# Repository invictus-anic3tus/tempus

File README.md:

<div align="center" width=100%>

  <p display="inline">

  <a href="https://hackclub.com/"></img></a>

  </p>

  <h1></h1>

  <p>
    An open source, ESP32-based smartwatch!
  </p>
</div>

<sub>This work is licensed under a
[Creative Commons Attribution-NonCommercial 4.0 International License](https://creativecommons.org/licenses/by-nc/4.0/).
</sub>

## Table of Contents

- [About](#about)
- [Features](#features)
- [Specifications](#specifications)
- [Bill of Materials](#bill-of-materials)
- [Contributing](#contributing)

## About

My name is Anicetus, and I love hardware. The Anicept Tempus is my newest addition to my brand, and the first devboard PCB! There are others out there, and many are probably much better. But I felt it was high time I had one of my _own._ It might not beat the competition in price, features, quality, you name it; but there comes a certain satisfaction when you can wear (more like tout at this point) a semi-stylish, functional, and helpful item that you can point to and confidently say: "I created this from scratch."

And so, the Tempus is a small yet powerful ESP32 devboard PCB + case, equipped with all the features that a modern digital smartwatch would need. Fully able to track steps and gestures, voice text, make beeps and alerts with a buzzer, power a round touchscreen, and, of course, tell time, it's the ideal replacement for a multi-hundred-dollar smartwatch with the same features.

## Features

Speaking of features, this watch is equipped with the following:
- A precise, quick gyroscope/accelerometer for hand tracking
- WiFi and Bluetooth for connecting to your phone to receive texts and calls, as well as control music apps such as Spotify
- An RTC (Real Time Clock) chip capable of maintaining incredibly accurate time
- A vibration motor for alerts and ringtones
- A microphone for voice messaging or reminders. (Note: the watch doesn't have a speaker, so playing music, receiving calls, etc. must be done through headphones connected to a phone connected to the watch. Also, unfortunately the ESP32-S3 cannot be used as a microphone during calls, so for that you'll need to use your phone's built-in mic.)
- Two reprogrammable buttons, perfect for quick text replies, controlling music, or navigating to apps.
- A modern USB-C 2.0 charging and programming recepticle
- A 500mAh battery, to ensure minimal charging time
- A battery percentage monitor to ensure the watch never dies
- A 1.28" capacitive touch display

## How do I build this?

Good question! If you'd like to make the Tempus for yourself, there's a few things you should keep in mind:
1. You must have access to a 3D printer or be willing to pay for a printing service. TPU or another flexible filament is required for the watch band.
2. You must have access to soldering equipment and be skilled in soldering. This includes a hot air gun and solder paste.
3. This design necessitates a custom PCB. These can get expensive if you need to account for shipping or tariff costs.
4. This is _not_ a professional design! I'm a random guy from the internet who made a smartwatch design; if you want to make it for yourself, go ahead! But I am not responsible for any misuse or unintended happenings due to faulty design.
5. Commercial use is not allowed. You cannot make this watch to sell to anybody.

Alright! Now we can get into how to actually build it. First, download the gerber.zip file in the PCB_Production folder, go to your favorite PCB manufacturing service (JLCPCB and PCBWay are good) and upload it in their quote system. It should say four-layer PCB. Here are the settings to select:
(Make sure you know what you're doing before changing these! The color is self-explanatory, but colors other than green can be more expensive.)

Then, order the DigiKey parts in [this cart](https://www.digikey.com/short/2mbbn5n0) and the screen from [BuyDisplay](https://www.buydisplay.com/1-28-inch-tft-lcd-display-240x240-round-circle-screen-for-smart-watch) or [eBay](https://www.ebay.com/itm/305668452899?var=604666595108).

Next, 3D print the files in the CAD folder. Detailed assembly instructions coming soon; for now, please reference the full CAD design!

## Specifications

Nerd info incoming
- Main processor: ESP32-S3-Wroom-1
- Gyroscope/accelerometer: LSM6DSMTR
- RTC: DS3231M+
- Battery Charging: TPB4056B (A drop-in TP4056 replacement, available on DigiKey)
- Microphone: SPH0645LM4H-B
- Display: [1.28 inch 240x240 IPS TFT LCD Round Circle Capacitive Touch Screen](https://www.buydisplay.com/1-28-inch-tft-lcd-display-240x240-round-circle-screen-for-smart-watch)
- Main 3v3 Buck-Boost Converter: TPS63031DSKR

## Bill of Materials

|       Item       |  Price  |                                                  Link                                              | Shipping |
|------------------|---------|----------------------------------------------------------------------------------------------------|----------|
| PCB              | $2      | <https://jlcpcb.com>                                                                               | $3.18    |
| DigiKey Parts*   | $67.34  | <https://www.digikey.com/short/2mbbn5n0>                                                           | $6.99    |
| Screen           | $8.85   | <https://www.buydisplay.com/1-28-inch-tft-lcd-display-240x240-round-circle-screen-for-smart-watch> | $8.12    |
| Total            | $78.19  |                                                                                                    | $18.29   |

*Including subjective tariffs, taxes, etc. Also includes battery and solder paste.

An online DigiKey cart is available at <https://www.digikey.com/short/2mbbn5n0>.

### Grand Total: ±$96.48

(Recommended planned price: $100)

## Contributing

<sub>aha somebody wishes to help me i see</sub>

If you'd like to request changes, suggest additions, or forcefully make me edit things, feel free to contact me via email (`me at anicetus dot dev`, preferred) or Discord (anic3tus).

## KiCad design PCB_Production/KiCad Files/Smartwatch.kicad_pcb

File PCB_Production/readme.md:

PCB Source files (schematic, board layout, etc.)

As this watch was designed to be hand-soldered, the assembly files have not been tested. The BOM, however, does contain LCSC part numbers for every component on the PCB. The gerbers are tested and work correctly.

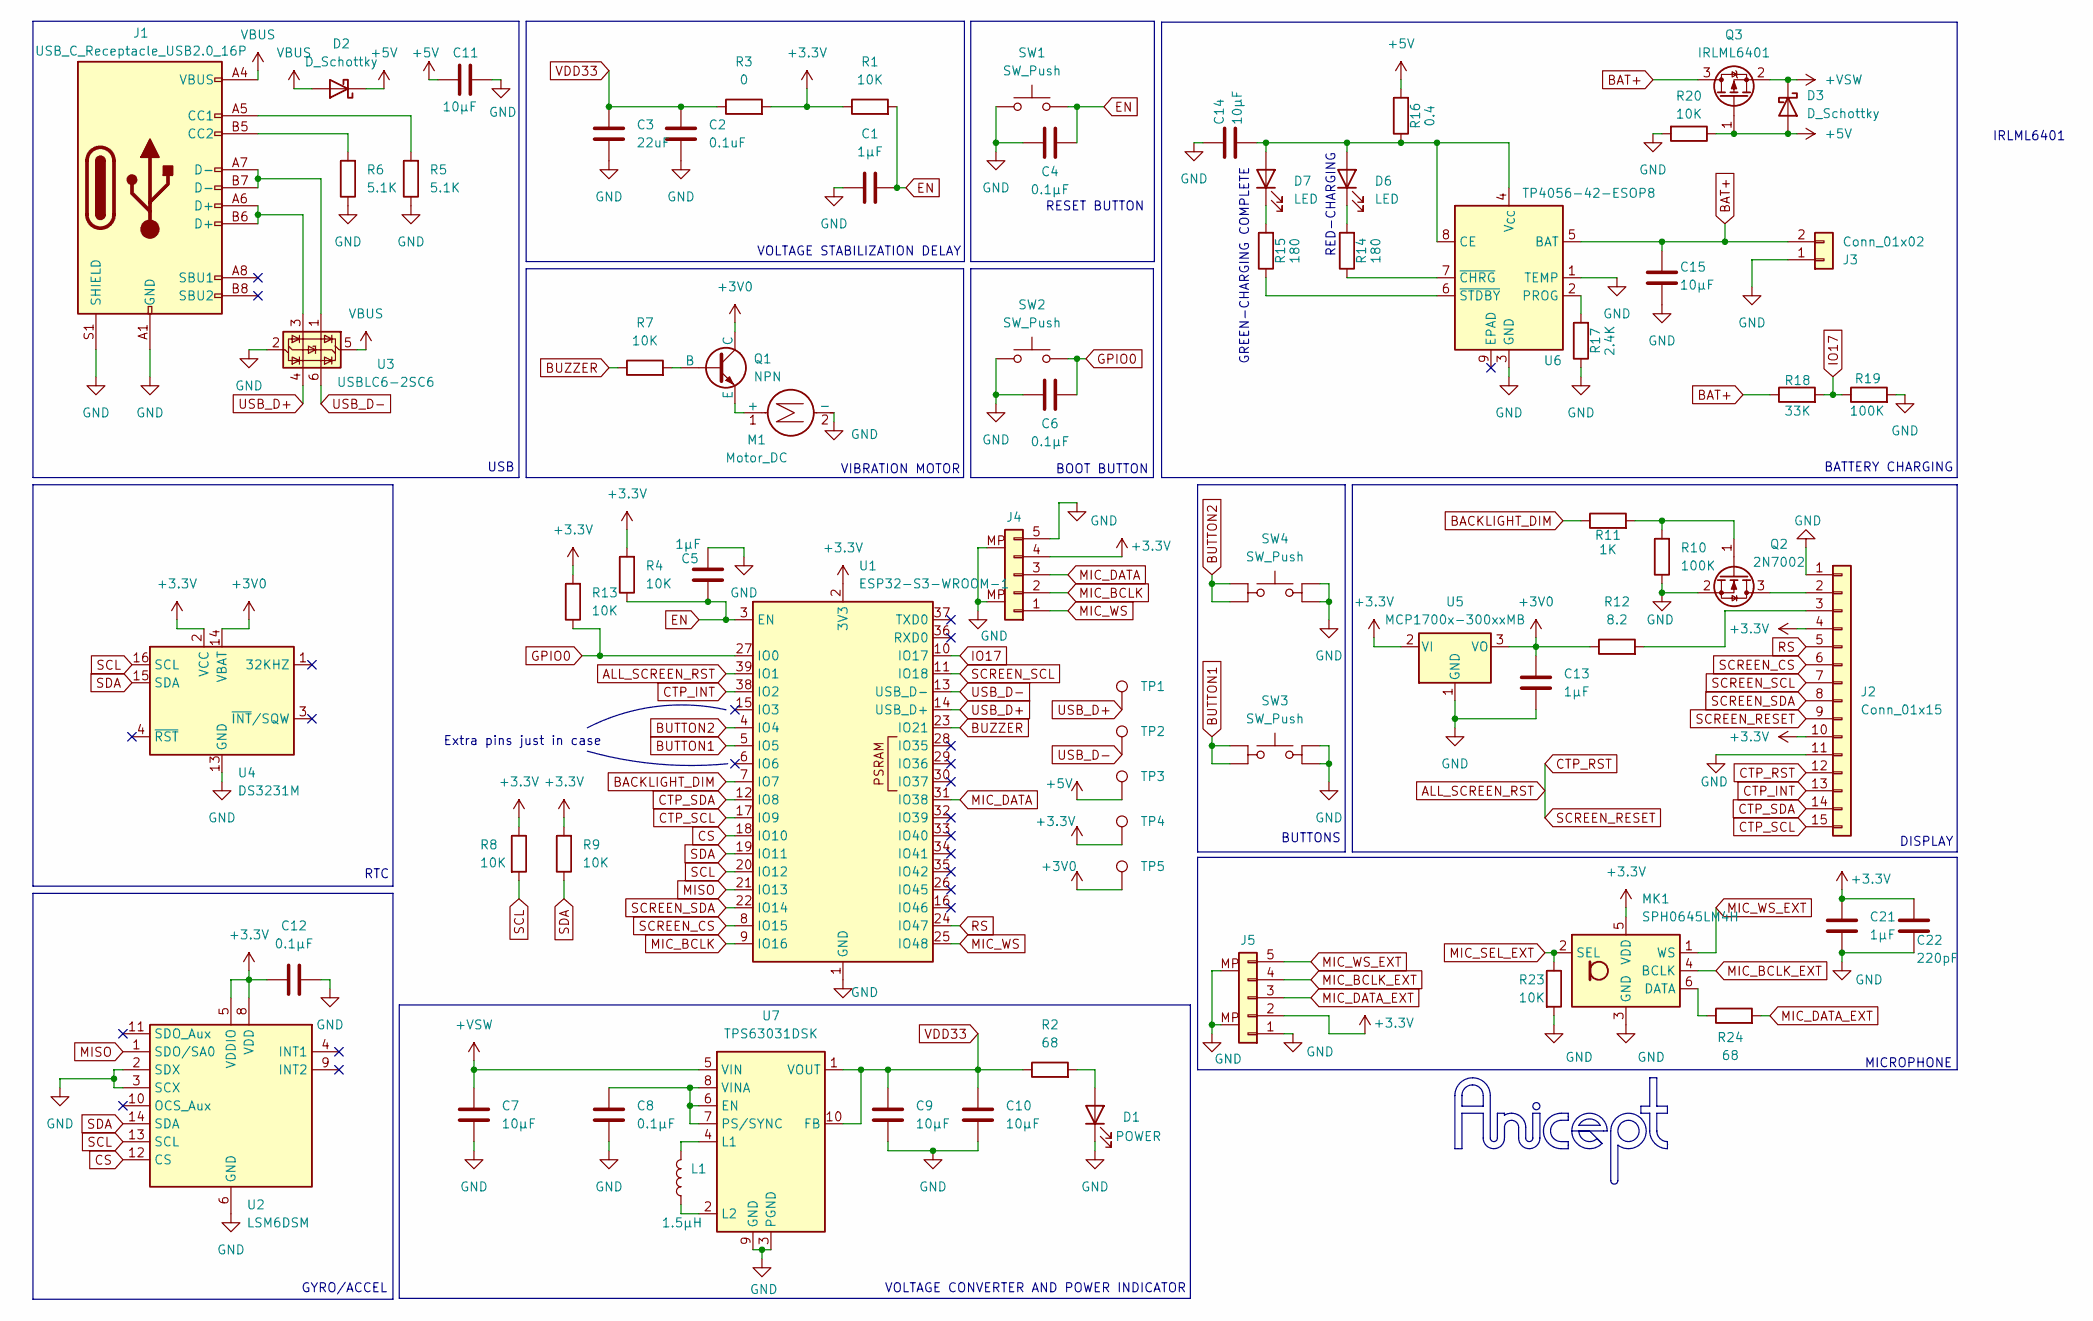
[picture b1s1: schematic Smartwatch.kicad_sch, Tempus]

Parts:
C1, C5, C13, C21: 1µF; C_0805_2012Metric
C2: 0.1uF; C_0805_2012Metric
C3: 22uF; C_0805_2012Metric
C4, C6, C8, C12: 0.1µF; C_0805_2012Metric
C7, C9, C10, C11, C14, C15: 10µF; C_0805_2012Metric
C22: 220pF; C_0805_2012Metric
D1: POWER; LED_0805_2012Metric
D2, D3: D_Schottky; D_SOD-123
D6, D7: LED; LED_0805_2012Metric
J1: USB_C_Receptacle_USB2.0_16P; USB_C_Receptacle_G-Switch_GT-USB-7010ASV
J2: Conn_01x15; Amphenol_F32Q-1A7x1-11015_1x15-1MP_P0.5mm_Horizontal
J3: Conn_01x02; JST_ZH_B2B-ZR_1x02_P1.50mm_Vertical
J4, J5: JST_SH_BM05B-SRSS-TB_1x05-1MP_P1.00mm_Vertical
L1: 1.5µH; IND_LQH3NPN1R5MJRL
M1: Motor_DC; TestPoint_Pad_1.5x1.5mm
MK1: SPH0645LM4H; Knowles_SPH0645LM4H-6_3.5x2.65mm
Q1: NPN; SOT-23
Q2: 2N7002; SOT-23
Q3: IRLML6401; SOT-23
R1, R4, R7, R8, R9, R13, R20, R23: 10K; R_0805_2012Metric
R2, R24: 68; R_0805_2012Metric
R3: 0; R_0805_2012Metric
R5, R6: 5.1K; R_0805_2012Metric
R10, R19: 100K; R_0805_2012Metric
R11: 1K; R_0805_2012Metric
R12: 8.2; R_0805_2012Metric
R14, R15: 180; R_0805_2012Metric
R16: 0.4; R_0805_2012Metric
R17: 2.4K; R_0805_2012Metric
R18: 33K; R_0805_2012Metric
SW1, SW2: SW_Push; SW-SMD_L3.9-W3.0-P4.45
SW3, SW4: SW_Push; SW_EVQ-P7C01P
TP1, TP2, TP3, TP4, TP5: TestPoint_Pad_1.0x1.0mm
U1: ESP32-S3-WROOM-1
U2: LSM6DSM; LGA-14_3x2.5mm_P0.5mm_LayoutBorder3x4y
U3: USBLC6-2SC6; SOT-23-6_Handsoldering
U4: DS3231M; SOIC-16W_7.5x10.3mm_P1.27mm
U5: MCP1700x-300xxMB; SOT-89-3
U6: TP4056-42-ESOP8; SOIC-8-1EP_3.9x4.9mm_P1.27mm_EP2.41x3.3mm_ThermalVias
U7: TPS63031DSK; WSON-10-1EP_2.5x2.5mm_P0.5mm_EP1.2x2mm_ThermalVias

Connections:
+3.3V: C12.2, C21.2, C22.2, J2.4, J2.10, J4.4, J5.2, MK1.5 (VDD), R1.1, R3.2, R4.2, R8.1, R9.2, R13.2, TP4.1, U1.2 (3V3), U2.5 (VDDIO), U2.8 (VDD), U4.2 (VCC), U5.2 (VI)
+3V0: C13.2, Q1.1 (C), R12.1, TP5.1, U4.14 (VBAT), U5.3 (VO)
+5V: C11.2, D2.1 (K), D3.2 (A), Q3.1 (G), R16.2, R20.1, TP3.1
+VSW: C7.2, D3.1 (K), Q3.2 (S), U7.5 (VIN)
ALL_SCREEN_RST: J2.9, J2.12, U1.39 (IO1)
BACKLIGHT_DIM: R11.1, U1.7 (IO7)
BAT+: C15.2, J3.2, Q3.3 (D), R18.1, U6.5 (BAT)
BUTTON1: SW3.1_1, SW3.1_2, U1.5 (IO5)
BUTTON2: SW4.1_1, SW4.1_2, U1.4 (IO4)
BUZZER: R7.1, U1.23 (IO21)
CS: U1.18 (IO10), U2.12 (CS)
CTP_INT: J2.13, U1.38 (IO2)
CTP_SCL: J2.15, U1.17 (IO9)
CTP_SDA: J2.14, U1.12 (IO8)
EN: C1.2, C4.1, C5.1, R1.2, R4.1, SW1.2, U1.3 (EN)
GND: C1.1, C2.1, C3.1, C4.2, C5.2, C6.2, C7.1, C8.1, C9.1, C10.1, C11.1, C12.1, C13.1, C14.2, C15.1, C21.1, C22.1, D1.1 (K), J1.A1 (GND), J1.A12 (GND), J1.B1 (GND), J1.B12 (GND), J1.S1 (SHIELD), J2.1, J2.11, J3.1, J4.5, J4.MP, J5.1, J5.MP, M1.2 (-), MK1.3 (GND), Q2.2 (S), R5.1, R6.1, R10.1, R17.1, R19.2, R20.2, R23.2, SW1.1, SW2.1, SW3.2_1, SW3.2_2, SW4.2_1, SW4.2_2, U1.1 (GND), U1.40 (GND), U1.41 (GND), U2.2 (SDX), U2.3 (SCX), U2.6 (GND), U2.7 (GND), U3.2 (GND), U4.5 (GND), U4.6 (GND), U4.7 (GND), U4.8 (GND), U4.9 (GND), U4.10 (GND), U4.11 (GND), U4.12 (GND), U4.13 (GND), U5.1 (GND), U6.1 (TEMP), U6.3 (GND), U7.3 (PGND), U7.9 (GND), U7.11 (PGND)
GPIO0: C6.1, R13.1, SW2.2, U1.27 (IO0)
IO17: R18.2, R19.1, U1.10 (IO17)
MIC_BCLK: J4.2, U1.9 (IO16)
MIC_BCLK_EXT: J5.4, MK1.4 (BCLK)
MIC_DATA: J4.3, U1.31 (IO38)
MIC_DATA_EXT: J5.3, R24.2
MIC_SEL_EXT: MK1.2 (SEL), R23.1
MIC_WS: J4.1, U1.25 (IO48)
MIC_WS_EXT: J5.5, MK1.1 (WS)
MISO: U1.21 (IO13), U2.1 (SDO/SA0)
unnamed: D1.2 (A), R2.2
unnamed: C14.1, D6.2 (A), D7.2 (A), R16.1, U6.4 (V_{CC}), U6.8 (CE)
unnamed: D6.1 (K), R14.2
unnamed: D7.1 (K), R15.2
unnamed: J1.A5 (CC1), R5.2
unnamed: J1.B5 (CC2), R6.2
unnamed: J1.A6 (D+), J1.B6 (D+), U3.3 (I/O2)
unnamed: J1.A7 (D-), J1.B7 (D-), U3.1 (I/O1)
unnamed: J2.2, Q2.3 (D)
unnamed: J2.3, R12.2
unnamed: M1.1 (+), Q1.3 (E)
unnamed: MK1.6 (DATA), R24.1
unnamed: Q1.2 (B), R7.2
unnamed: Q2.1 (G), R10.2, R11.2
unnamed: R17.2, U6.2 (PROG)
unnamed: R14.1, U6.7 (~CHRG)
unnamed: R15.1, U6.6 (~STDBY)
unnamed: C8.2, U7.6 (EN), U7.7 (PS/SYNC), U7.8 (VINA)
unnamed: L1.2, U7.4 (L1)
unnamed: L1.1, U7.2 (L2)
RS: J2.5, U1.24 (IO47)
SCL: R8.2, U1.20 (IO12), U2.13 (SCL), U4.16 (SCL)
SCREEN_CS: J2.6, U1.8 (IO15)
SCREEN_SCL: J2.7, U1.11 (IO18)
SCREEN_SDA: J2.8, U1.22 (IO14)
SDA: R9.1, U1.19 (IO11), U2.14 (SDA), U4.15 (SDA)
USB_D+: TP1.1, U1.14 (USB_D+), U3.4 (I/O2)
USB_D-: TP2.1, U1.13 (USB_D-), U3.6 (I/O1)
VBUS: D2.2 (A), J1.A4 (VBUS), J1.A9 (VBUS), J1.B4 (VBUS), J1.B9 (VBUS), U3.5 (VBUS)
VDD33: C2.2, C3.2, C9.2, C10.2, R2.1, R3.1, U7.1 (VOUT), U7.10 (FB)

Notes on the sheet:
MICROPHONE
VIBRATION MOTOR
USB
VOLTAGE STABILIZATION DELAY
BUTTONS
BATTERY CHARGING
RTC
Extra pins just in case
BOOT BUTTON
RESET BUTTON
IRLML6401
GYRO/ACCEL
VOLTAGE CONVERTER AND POWER INDICATOR
GREEN-CHARGING COMPLETE
DISPLAY
RED-CHARGING

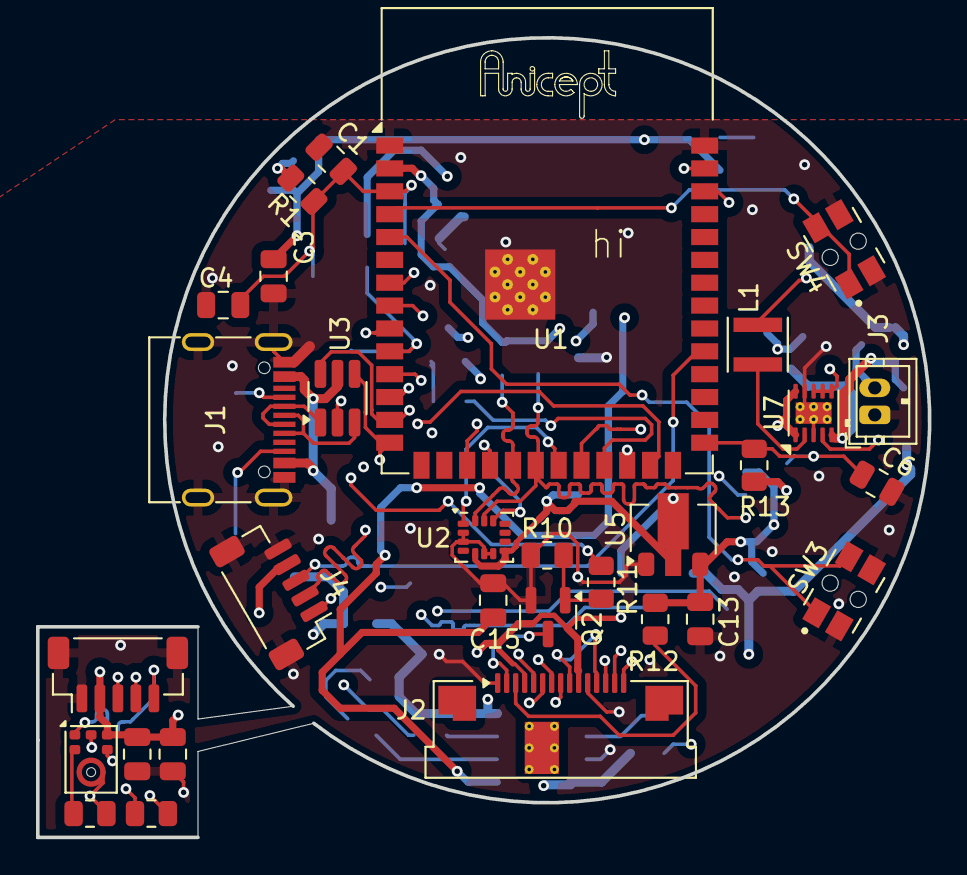
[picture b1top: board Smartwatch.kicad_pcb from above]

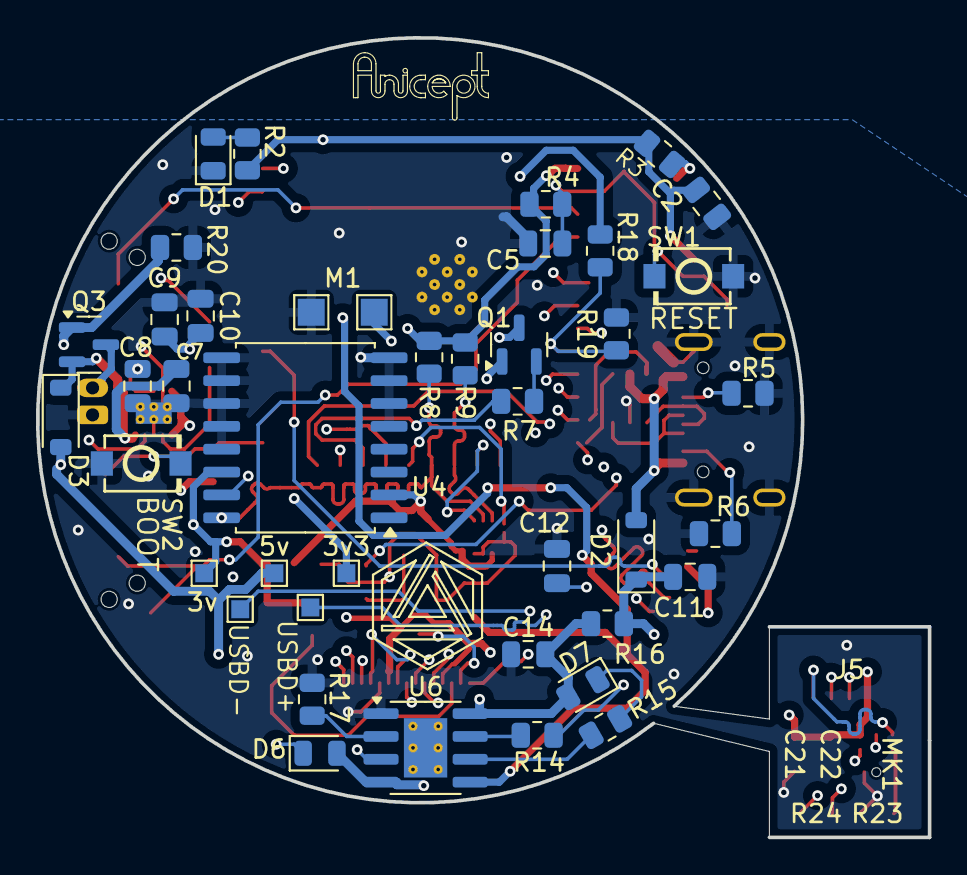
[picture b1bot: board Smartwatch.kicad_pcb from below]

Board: 4 copper layers, 49.5 x 44.4 mm, 71 parts (41 on the bottom side), 56 nets.

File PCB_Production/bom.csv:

Designator,Footprint,Quantity,Value,LCSC Part #
BZ1,BUZ-SMD_L5.0-W5.5-P4.60,1,Buzzer,
"C1, C13, C21, C5",0805,4,1µF,
"C10, C11, C14, C15, C7, C9",0805,6,10µF,
"C12, C4, C6, C8",0805,4,0.1µF,
C2,0805,1,0.1uF,
C22,0805,1,220pF,
C3,0805,1,22uF,
D1,0805,1,POWER,
D2,D_SOD-123,1,D_Schottky,
"D3, D4, D5",0603,3,D_TVS,
"D6, D7",0805,2,LED,
J1,USB_C_Receptacle_G-Switch_GT-USB-7010ASV,1,USB_C_Receptacle_USB2.0_16P,
J2,Amphenol_F32Q-1A7x1-11015_1x15-1MP_P0.5mm_Horizontal,1,Conn_01x15,
J3,JST_ZH_B2B-ZR_1x02_P1.50mm_Vertical,1,Conn_01x02,
"J4, J5",JST_SH_BM05B-SRSS-TB_1x05-1MP_P1.00mm_Vertical,2,JST_SH_BM05B-SRSS-TB_1x05-1MP_P1.00mm_Vertical,
L1,L_Coilcraft_LPS3010,1,1.5µH,
MK1,Knowles_SPH0645LM4H-6_3.5x2.65mm,1,SPH0645LM4H,
Q1,SOT-23,1,NPN,
Q2,SOT-23,1,2N7002,
"R1, R13, R23, R4, R7, R8, R9",0805,7,10K,
"R10, R19",0805,2,100K,
"R11, R15",0805,2,1K,
R12,0805,1,8.2,
R14,0805,1,2.2K,
R16,0805,1,0.4,
R17,0805,1,5K,
R18,0805,1,33K,
"R2, R24",0805,2,68,
R3,0805,1,0,
"R5, R6",0805,2,5.1K,
"SW1, SW2",SW-SMD_L3.9-W3.0-P4.45,2,SW_Push,
"SW3, SW4",SW_THT_Right_Angle_118250274,2,SW_Push,
U1,ESP32-S3-WROOM-1,1,ESP32-S3-WROOM-1,
U2,LGA-14_3x2.5mm_P0.5mm_LayoutBorder3x4y,1,LSM6DSM,
U4,SOIC-16W_7.5x10.3mm_P1.27mm,1,DS3231M,
U5,SOT-89-3,1,MCP1700x-300xxMB,
U6,SOIC-8-1EP_3.9x4.9mm_P1.27mm_EP2.41x3.3mm_ThermalVias,1,TP4056-42-ESOP8,
U7,WSON-10-1EP_2.5x2.5mm_P0.5mm_EP1.2x2mm_ThermalVias,1,TPS63031DSK,

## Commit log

2025-09-19 Rename image.png to Schematic.png
2025-12-30 Update README.md - new title image
2025-12-31 Add code and update images
    Added Claude AI generated code for Arduino IDE, and updated images to reflect the current PCB
2026-03-27 Updated some production files
2026-03-29 Update CAD, PCB, BOM
2026-03-29 Removed outdated images, moved old journal
2026-04-01 added schem to readme cuz manan is a dummy
